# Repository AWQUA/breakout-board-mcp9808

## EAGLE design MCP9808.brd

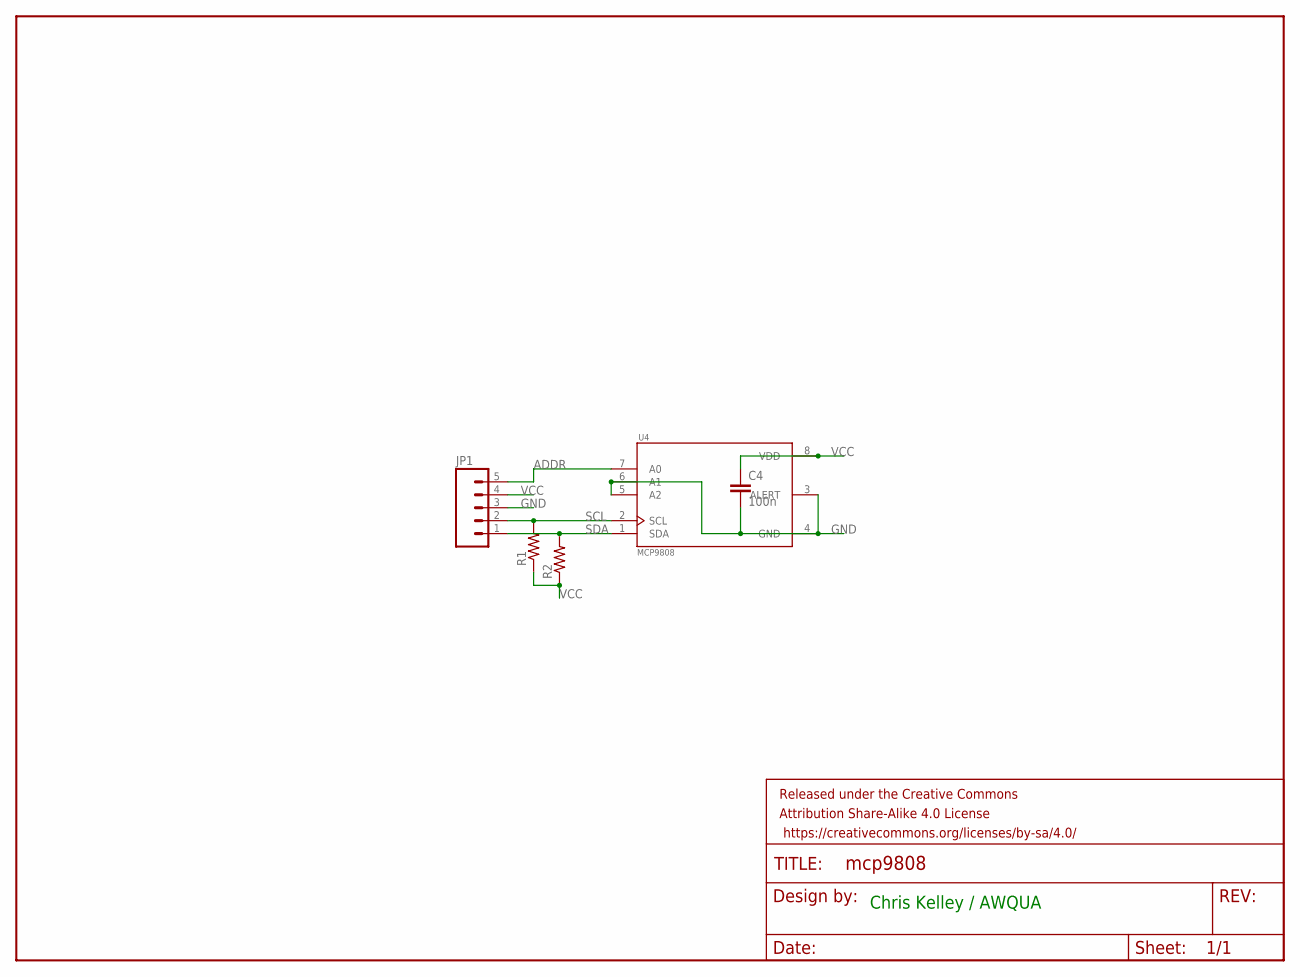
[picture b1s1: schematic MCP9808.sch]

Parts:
C4: 100n; 0603-CAP
FRAME1: FRAME-LETTER; CREATIVE_COMMONS
JP1: M05PTH; 1X05
R1, R2: RESISTOR0603-RES; 0603-RES
U4: MCP9808; SOP65P490X110-8N

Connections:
ADDR: JP1.5, U4.7 (A0)
GND: C4.2, JP1.3, U4.3 (ALERT), U4.4 (GND), U4.5 (A2), U4.6 (A1)
SCL: JP1.2, R1.2, U4.2 (SCL)
SDA: JP1.1, R2.2, U4.1 (SDA)
VCC: C4.1, JP1.4, R1.1, R2.1, U4.8 (VDD)

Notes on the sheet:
Chris Kelley / AWQUA

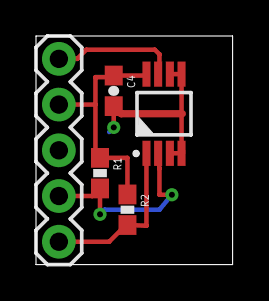
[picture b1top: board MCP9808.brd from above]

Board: 2 copper layers, 10.9 x 12.7 mm, 6 parts (0 on the bottom side), 5 nets.

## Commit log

2017-03-08 board added

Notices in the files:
parts and their libraries:
SparkFun-Aesthetics: Licensing: Creative Commons ShareAlike 4.0 International - https://creativecommons.org/licenses/by-sa/4.0
SparkFun-Aesthetics: Released under the Creative Commons Attribution Share-Alike 4.0 License
SparkFun-Aesthetics: https://creativecommons.org/licenses/by-sa/4.0
